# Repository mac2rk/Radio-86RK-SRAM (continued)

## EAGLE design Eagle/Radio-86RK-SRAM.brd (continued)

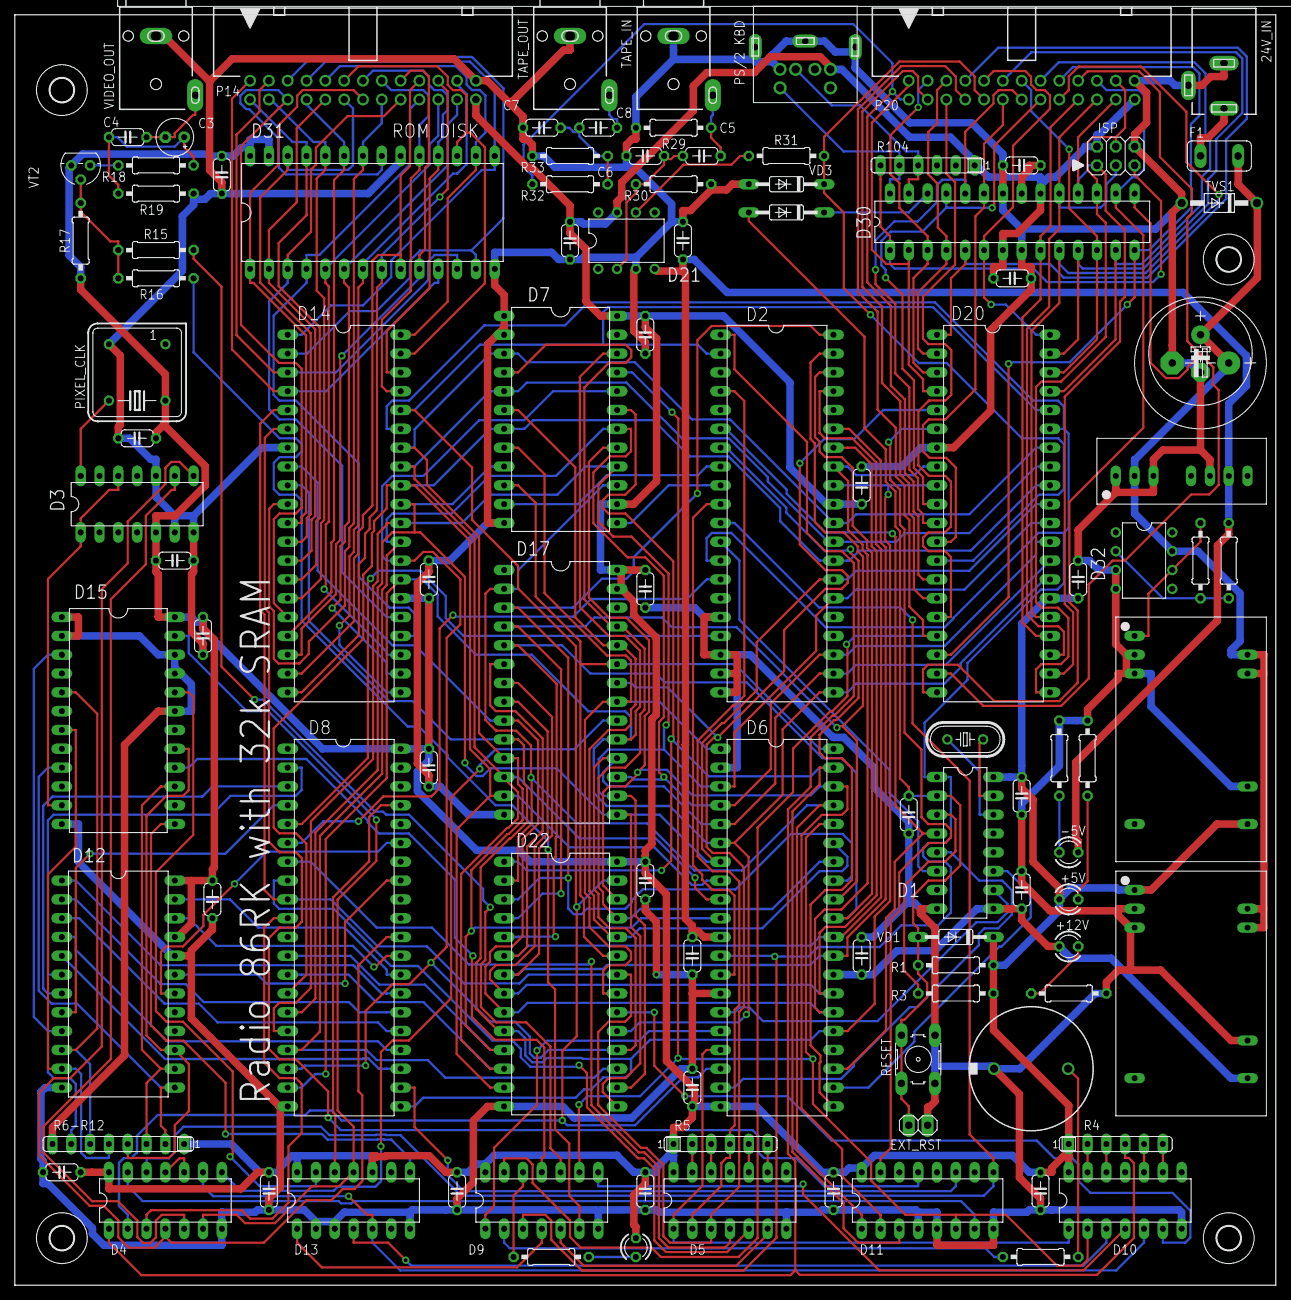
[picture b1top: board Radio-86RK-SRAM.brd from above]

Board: 2 copper layers, 170.2 x 171.4 mm, 111 parts (0 on the bottom side), 177 nets.

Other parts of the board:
C: 3,2
F: 3,2
H: 3,2
J: 3,2
